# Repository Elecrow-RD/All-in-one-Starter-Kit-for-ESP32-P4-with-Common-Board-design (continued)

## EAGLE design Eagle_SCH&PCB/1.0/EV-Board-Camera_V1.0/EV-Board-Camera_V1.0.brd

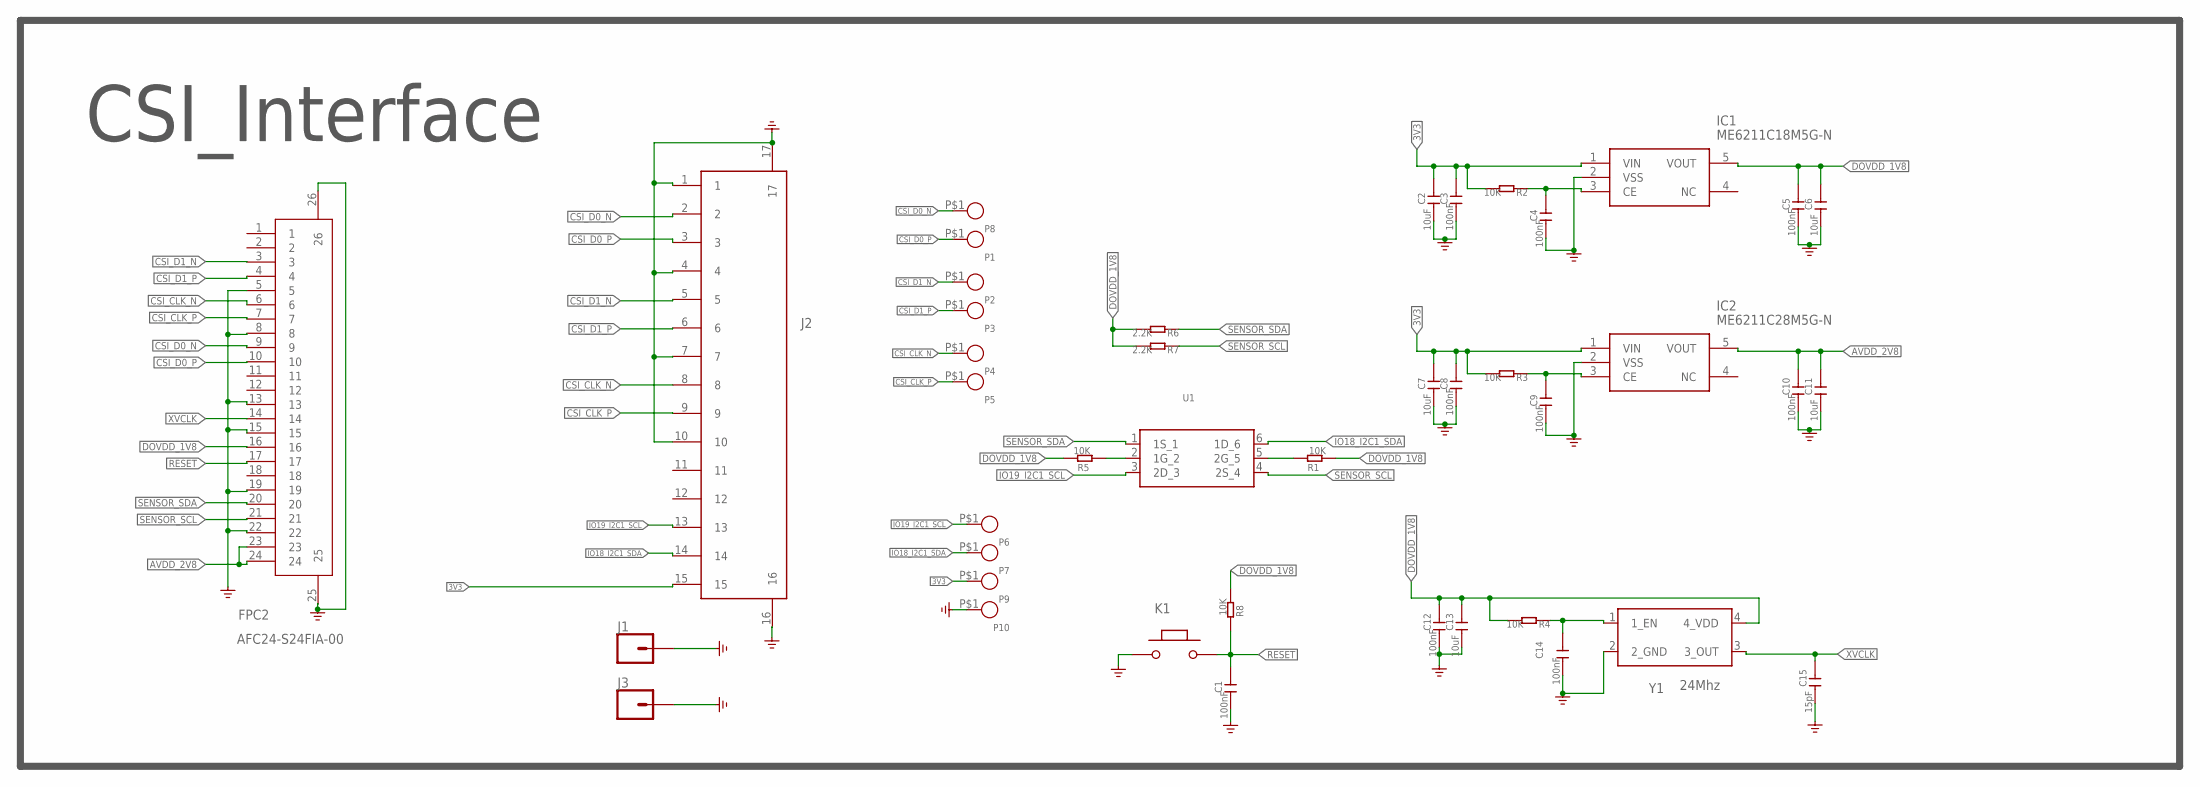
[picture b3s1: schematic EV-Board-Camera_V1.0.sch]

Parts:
C1, C3, C4, C5, C8, C9, C10, C12, C14: 100nF; C0402
C2, C6, C7, C11, C13: 10uF; C0402
C15: 15pF; C0402
FPC2: AFC24-S24FIA-00; FPC-SMD_P0.50-24P_QCHF-SM-H2.0
IC1: ME6211C18M5G-N; SOT95P282X145-5N
IC2: ME6211C28M5G-N; SOT95P282X145-5N
J1, J3: CONN_01_3.1MM_SMD1X01_3.1MM_SMD; 1X01_2MM
J2: C262349_15P_1MM_下接_AFA07-S15FCC-00
K1: BUTTON; 157SW
P1, P2, P3, P4, P5, P6, P7, P8, P9, P10: TEST_PADPAD-1.5MM; TEST_PAD-1.5MM
R1, R2, R3, R4, R5, R8: 10K; R0402
R6, R7: 2.2K; R0402
U1: WST2006
Y1: 24Mhz; 24MHZ_1631-24003-BTKEYA

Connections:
3V3: C2.2, C3.2, C7.2, C8.2, IC1.1 (VIN), IC2.1 (VIN), J2.15, P9.P$1, R2.2, R3.2
AVDD_2V8: C10.2, C11.2, FPC2.23, FPC2.24, IC2.5 (VOUT)
CSI_CLK_N: FPC2.6, J2.8, P4.P$1
CSI_CLK_P: FPC2.7, J2.9, P5.P$1
CSI_D0_N: FPC2.9, J2.2, P8.P$1
CSI_D0_P: FPC2.10, J2.3, P1.P$1
CSI_D1_N: FPC2.3, J2.5, P2.P$1
CSI_D1_P: FPC2.4, J2.6, P3.P$1
DOVDD_1V8: C5.2, C6.2, C12.2, C13.2, FPC2.16, IC1.5 (VOUT), R1.1, R4.2, R5.2, R6.2, R7.2, R8.1, Y1.4 (4_VDD)
GND: C1.1, C2.1, C3.1, C4.1, C5.1, C6.1, C7.1, C8.1, C9.1, C10.1, C11.1, C12.1, C13.1, C14.1, C15.1, FPC2.5, FPC2.8, FPC2.13, FPC2.15, FPC2.19, FPC2.22, FPC2.25, FPC2.26, IC1.2 (VSS), IC2.2 (VSS), J1.1, J2.1, J2.4, J2.7, J2.10, J2.16, J2.17, J3.1, K1.1, P10.P$1, Y1.2 (2_GND)
IO18_I2C1_SDA: J2.14, P7.P$1, U1.6 (1D_6)
IO19_I2C1_SCL: J2.13, P6.P$1, U1.3 (2D_3)
unnamed: R5.1, U1.2 (1G_2)
unnamed: C4.2, IC1.3 (CE), R2.1
unnamed: R1.2, U1.5 (2G_5)
unnamed: C9.2, IC2.3 (CE), R3.1
unnamed: C14.2, R4.1, Y1.1 (1_EN)
RESET: C1.2, FPC2.17, K1.2, R8.2
SENSOR_SCL: FPC2.21, R7.1, U1.4 (2S_4)
SENSOR_SDA: FPC2.20, R6.1, U1.1 (1S_1)
XVCLK: C15.2, FPC2.14, Y1.3 (3_OUT)

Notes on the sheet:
CSI_Interface

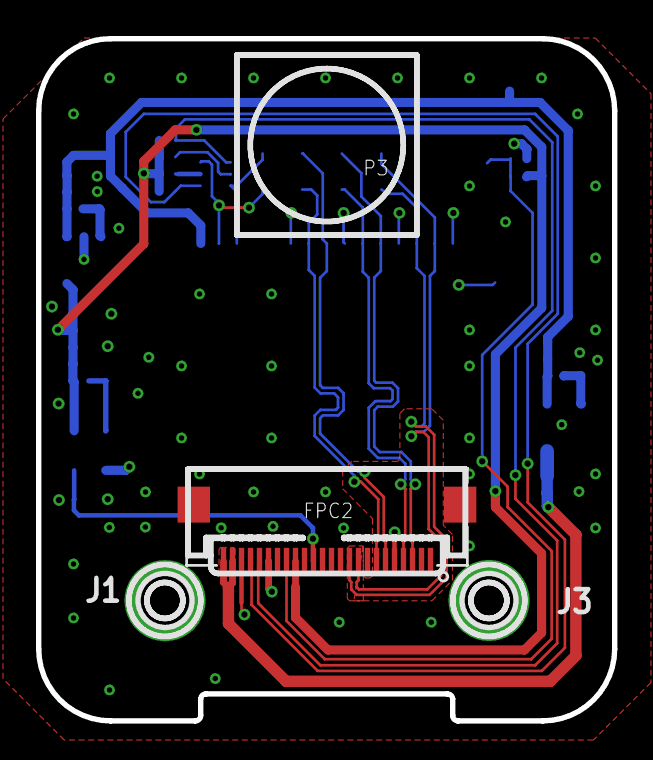
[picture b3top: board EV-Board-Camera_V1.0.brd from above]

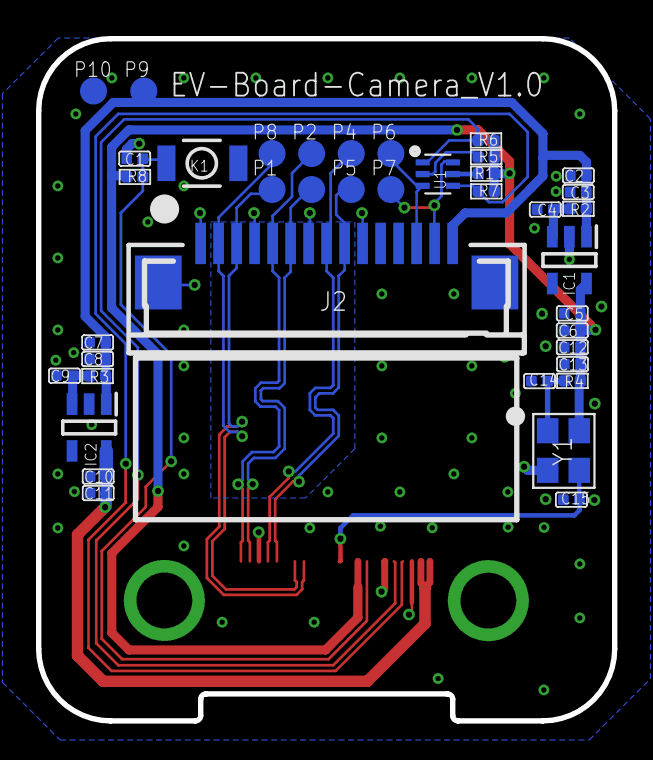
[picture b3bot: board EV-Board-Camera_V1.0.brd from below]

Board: 2 copper layers, 32.0 x 37.9 mm, 42 parts (39 on the bottom side), 21 nets.

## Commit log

2026-03-20 add arduino
2026-05-22 sync idf lesson20
